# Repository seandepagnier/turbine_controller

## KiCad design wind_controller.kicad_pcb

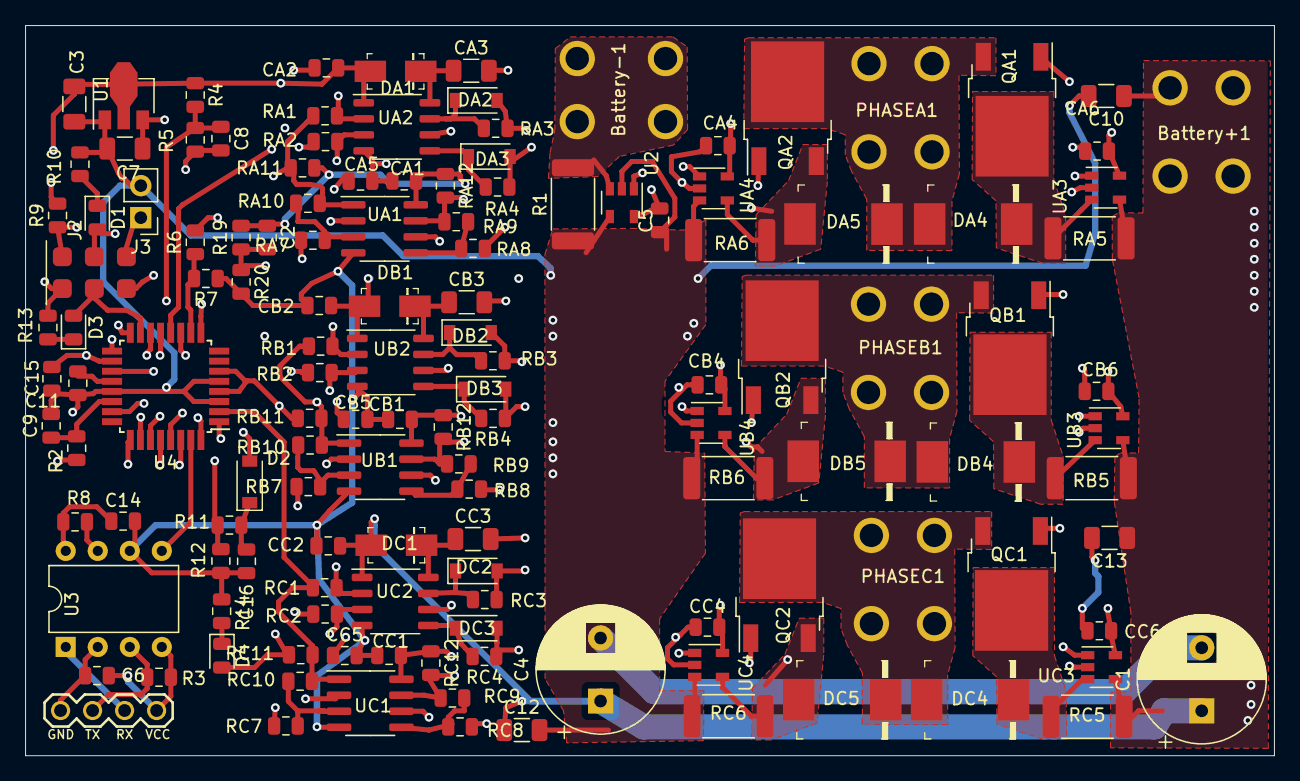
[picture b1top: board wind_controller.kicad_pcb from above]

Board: 4 copper layers, 99.1 x 57.9 mm, 135 parts (0 on the bottom side), 73 nets.

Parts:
Battery+1: Conn_01x01; screw_terminal
Battery-1: Conn_01x01; screw_terminal
C1, C4: 330uF; CP_Radial_D10.0mm_P5.00mm
C2, C9, C16: 1uF; C_0805_2012Metric
C3, C7, C10, C12, C13: 10uF; C_1206_3216Metric
C5, C6, C8, C11, C14, C15: .1uF; C_0805_2012Metric
CA1, CA4, CA5, CA6: .1uF; C_0805_2012Metric
CA2: 1uF; C_0805_2012Metric
CA3: 10uF; C_1206_3216Metric
CB1, CB4, CB5, CB6: .1uF; C_0805_2012Metric
CB2: 1uF; C_0805_2012Metric
CB3: 10uF; C_1206_3216Metric
CC1, CC4, CC5, CC6: .1uF; C_0805_2012Metric
CC2: 1uF; C_0805_2012Metric
CC3: 10uF; C_1206_3216Metric
D1: BLUE; LED_0805_2012Metric
D2: D; D_SOD-123
D3: GREEN; LED_0805_2012Metric
D4: RED; LED_0805_2012Metric
DA1: D; DO-214AC
DA2, DA3: D; D_SOD-123
DA4, DA5: D_Schottky; DO-214AB
DB1: D; DO-214AC
DB2, DB3: D; D_SOD-123
DB4, DB5: D_Schottky; DO-214AB
DC1: D; DO-214AC
DC2, DC3: D; D_SOD-123
DC4, DC5: D_Schottky; DO-214AB
J1: UART_Device; uart
J2: ISP
J3: start; PinHeader_1x02_P2.54mm_Vertical
PHASEA1: Conn_01x01; screw_terminal
PHASEB1: Conn_01x01; screw_terminal
PHASEC1: Conn_01x01; screw_terminal
QA1, QA2: nFET; TO-252-2
QB1, QB2: nFET; TO-252-2
QC1, QC2: nFET; TO-252-2
R1: .002; R_2512_6332Metric
R2, R5, R12: 100k; R_0805_2012Metric
R3, R8, R10, R13, R14: 2.4k; R_0805_2012Metric
R4, R11: 560k; R_0805_2012Metric
R6: 150k; R_0805_2012Metric
R7, R9, R20: 10k; R_0805_2012Metric
R19: 200k; R_0805_2012Metric
RA1, RA2: 100k; R_0805_2012Metric
RA3, RA4: 20; R_0805_2012Metric
RA5, RA6: .002; R_2512_6332Metric
RA7, RA8: 1k; R_0805_2012Metric
RA9, RA10: 200k; R_0805_2012Metric
RA11, RA12: 10k; R_0805_2012Metric
RB1, RB2: 100k; R_0805_2012Metric
RB3, RB4: 20; R_0805_2012Metric
RB5, RB6: .002; R_2512_6332Metric
RB7, RB8: 1k; R_0805_2012Metric
RB9, RB10: 200k; R_0805_2012Metric
RB11, RB12: 10k; R_0805_2012Metric
RC1, RC2: 100k; R_0805_2012Metric
RC3, RC4: 20; R_0805_2012Metric
RC5, RC6: .002; R_2512_6332Metric
RC7, RC8: 1k; R_0805_2012Metric
RC9, RC10: 200k; R_0805_2012Metric
RC11, RC12: 10k; R_0805_2012Metric
U1: HT75xx-1-SOT89; SOT-89-3
U2: INA180; SOT-23-5
U3: cpc5001; DIP-8_W7.62mm
U4: ATmega328-AU; TQFP-32_7x7mm_P0.8mm
UA1: LMV762; SOIC-8_3.9x4.9mm_P1.27mm
UA2: EG2132; SOP-8_3.9x4.9mm_P1.27mm
UA3, UA4: INA180; SOT-23-5
UB1: LMV762; SOIC-8_3.9x4.9mm_P1.27mm
UB2: EG2132; SOP-8_3.9x4.9mm_P1.27mm
UB3, UB4: INA180; SOT-23-5
UC1: LMV762; SOIC-8_3.9x4.9mm_P1.27mm
UC2: EG2132; SOP-8_3.9x4.9mm_P1.27mm
UC3, UC4: INA180; SOT-23-5

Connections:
+5V: C2.1, C5.1, C7.1, C14.1, C15.2, CA1.1, CA4.2, CA6.1, CB1.1, CB4.2, CB6.1, CC1.1, CC4.2, CC6.1, D4.2, J2.4, R8.2, R9.2, R19.2, RA11.1, RA12.1, RB11.1, RB12.1, RC11.1, RC12.1, U1.3, U2.5, U3.8, U4.4, U4.6, U4.18, UA1.8, UA3.5, UA4.5, UB1.8, UB3.5, UB4.5, UC1.8, UC3.5, UC4.5
/PhaseA/CURL: RA8.2, UA4.1
/PhaseB/CURL: RB8.2, UB4.1
/PhaseB/PHASE: CB3.2, DB4.2, DB5.1, PHASEB1.1, QB1.3, QB2.2, UB2.6
/PhaseC/CURL: RC8.2, UC4.1
/PhaseC/PHASE: CC3.2, DC4.2, DC5.1, PHASEC1.1, QC1.3, QC2.2, UC2.6
AH: RA1.1, U4.9, UA2.2
AHS: RA1.2, RA10.1, RA11.2, U4.32, UA1.1
AL: RA2.1, U4.26, UA2.3
ALS: RA2.2, RA9.1, RA12.2, U4.12, UA1.7
BH: RB1.1, U4.11, UB2.2
BHS: RB1.2, RB10.1, RB11.2, U4.1, UB1.1
BL: RB2.1, U4.27, UB2.3
BLS: RB2.2, RB9.1, RB12.2, U4.13, UB1.7
CH: RC1.1, U4.14, UC2.2
CHS: RC1.2, RC10.1, RC11.2, U4.2, UC1.1
CL: RC2.1, U4.28, UC2.3
CLS: RC2.2, RC9.1, RC12.2, U4.25, UC1.7
GND: C1.2, C3.2, C4.2, C5.2, C7.2, C8.2, C9.2, C10.2, C11.1, C12.2, C13.2, C14.2, C15.1, C16.2, CA1.2, CA2.2, CA5.2, CA6.2, CB1.2, CB2.2, CB5.2, CB6.2, CC1.2, CC2.2, CC5.2, CC6.2, J2.6, J3.2, R1.1, R5.2, R7.1, R10.2, R12.2, R13.2, R14.2, R20.2, RA6.1, RB6.1, RC6.1, U1.1, U2.2, U2.4, U3.6, U4.3, U4.5, U4.21, UA1.4, UA2.4, UA3.2, UA4.3, UB1.4, UB2.4, UB3.2, UB4.3, UC1.4, UC2.4, UC3.2, UC4.3
MISO: J2.1, J3.1, U4.16
MOSI: D3.2, J2.5, U4.15
unnamed: Battery-1.1, R1.2, U2.3
unnamed: C6.1, J1.1, R3.2, U3.4
unnamed: C6.2, J1.4, U3.2
unnamed: C8.1, R4.2, R5.1, U4.19
unnamed: C9.1, R2.2, U4.22
unnamed: C11.2, U4.20
unnamed: C16.1, D2.1, R11.1
unnamed: CA3.1, DA1.1, UA2.8
unnamed: CA4.1, DA5.2, QA2.3, RA6.2, UA4.2, UA4.4
unnamed: CB3.1, DB1.1, UB2.8
unnamed: CB4.1, DB5.2, QB2.3, RB6.2, UB4.2, UB4.4
unnamed: CC3.1, DC1.1, UC2.8
unnamed: CC4.1, DC5.2, QC2.3, RC6.2, UC4.2, UC4.4
unnamed: D1.1, R10.1
unnamed: D3.1, R13.1
unnamed: D4.1, R14.1
unnamed: DA2.1, RA3.2, UA2.7
unnamed: DA2.2, QA1.1, RA3.1
unnamed: DA3.1, RA4.2, UA2.5
unnamed: DA3.2, QA2.1, RA4.1
unnamed: DA4.1, QA1.2, RA5.1, UA3.3
unnamed: DB2.1, RB3.2, UB2.7
unnamed: DB2.2, QB1.1, RB3.1
unnamed: DB3.1, RB4.2, UB2.5
unnamed: DB3.2, QB2.1, RB4.1
unnamed: DB4.1, QB1.2, RB5.1, UB3.3
unnamed: DC2.1, RC3.2, UC2.7
unnamed: DC2.2, QC1.1, RC3.1
unnamed: DC3.1, RC4.2, UC2.5
unnamed: DC3.2, QC2.1, RC4.1
unnamed: DC4.1, QC1.2, RC5.1, UC3.3
unnamed: J1.2, U3.1
unnamed: J1.3, R3.1, U3.3
unnamed: R2.1, U2.1
unnamed: R6.1, R7.2, U4.10
unnamed: R11.2, R12.1, U4.23
unnamed: RA7.1, UA3.1
unnamed: RA8.1, RA9.2, UA1.5
unnamed: RA7.2, RA10.2, UA1.3
unnamed: RB7.1, UB3.1
unnamed: RB8.1, RB9.2, UB1.5
unnamed: RB7.2, RB10.2, UB1.3
unnamed: RC7.1, UC3.1
unnamed: RC8.1, RC9.2, UC1.5
unnamed: RC7.2, RC10.2, UC1.3
PHASEA: CA3.2, D2.2, DA4.2, DA5.1, PHASEA1.1, QA1.3, QA2.2, UA2.6
RESET: J2.3, R9.1, U4.29
RX: R8.1, U3.7, U4.30
SCK: D1.2, J2.2, U4.17
THRESH: C2.2, CA5.1, CB5.1, CC5.1, R19.1, R20.1, UA1.2, UA1.6, UB1.2, UB1.6, UC1.2, UC1.6
TX: U3.5, U4.31
VCC: Battery+1.1, C1.1, C3.1, C4.1, C10.1, C12.1, C13.1, CA2.1, CB2.1, CC2.1, DA1.2, DB1.2, DC1.2, R4.1, R6.2, RA5.2, RB5.2, RC5.2, U1.2, UA2.1, UA3.4, UB2.1, UB3.4, UC2.1, UC3.4

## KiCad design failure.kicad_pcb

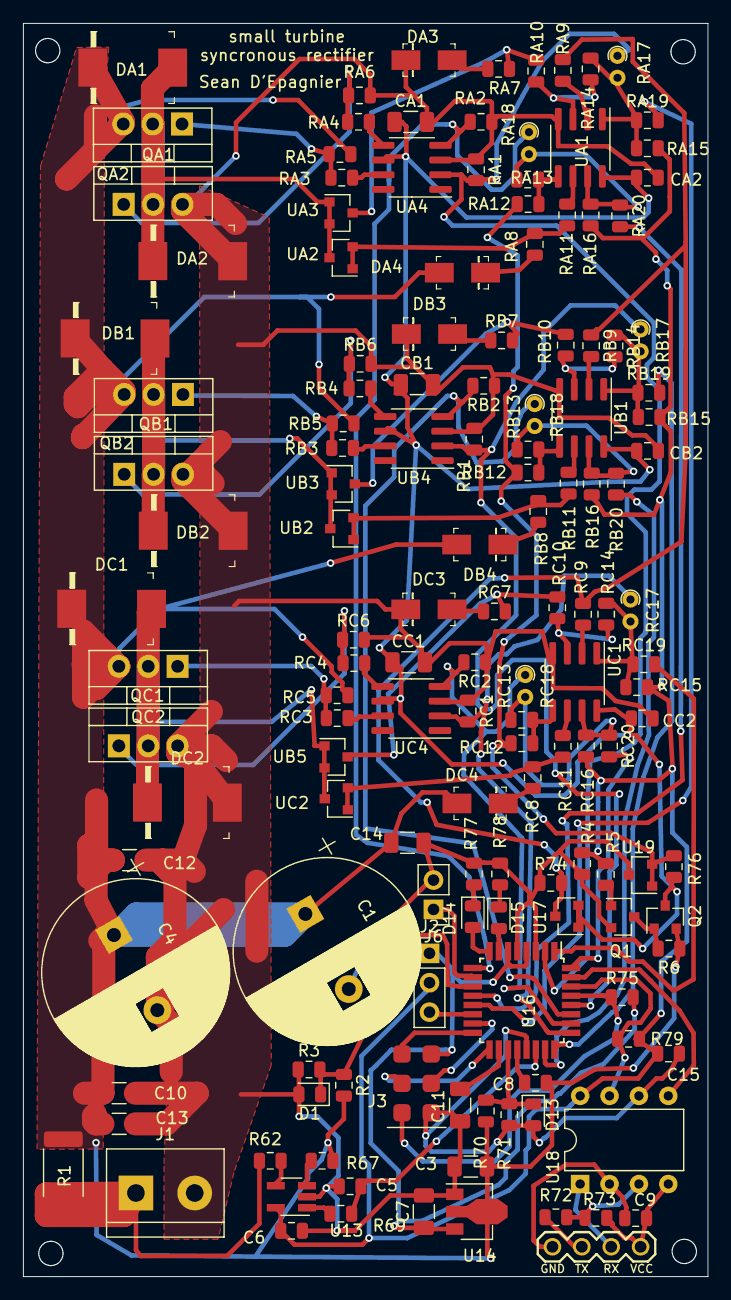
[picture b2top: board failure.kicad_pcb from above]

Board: 2 copper layers, 59.2 x 108.3 mm, 146 parts (0 on the bottom side), 92 nets.

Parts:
C1, C4: 680uF; CP_Radial_D16.0mm_P7.50mm
C3, C7, C10, C11, C12, C13, C14: 10uF; C_1206_3216Metric
C5: 1uF; C_0805_2012Metric
C6, C8, C9, C15: .1uF; C_0805_2012Metric
CA1: 10uF; C_1206_3216Metric
CA2: .1uF; C_0805_2012Metric
CB1: 10uF; C_1206_3216Metric
CB2: .1uF; C_0805_2012Metric
CC1: 10uF; C_1206_3216Metric
CC2: .1uF; C_0805_2012Metric
D1, D13: 3v3; D_0805_2012Metric
D14: RED; LED_0805_2012Metric
D15: BLUE; LED_0805_2012Metric
DA1, DA2: D_Schottky; DO-214AB
DA3, DA4: D; DO-214AC
DB1, DB2: D_Schottky; DO-214AB
DB3, DB4: D; DO-214AC
DC1, DC2: D_Schottky; DO-214AB
DC3, DC4: D; DO-214AC
J1: Conn_01x02; TerminalBlock_bornier-2_P5.08mm
J2: Conn_01x03; PinHeader_1x03_P2.54mm_Vertical
J3: ISP
J5: UART_Device; uart
J6: Stop; PinHeader_1x02_P2.54mm_Vertical
Q1: npn; SOT-23
Q2: pFET; SOT-23
QA1: pFET; TO-220-3_Vertical
QA2: nFET; TO-220-3_Vertical
QB1: pFET; TO-220-3_Vertical
QB2: nFET; TO-220-3_Vertical
QC1: pFET; TO-220-3_Vertical
QC2: nFET; TO-220-3_Vertical
R1: .002; R_2512_6332Metric
R2: 150k; R_0805_2012Metric
R3, R6, R71, R75: 10k; R_0805_2012Metric
R4, R5, R69, R74, R76: 100k; R_0805_2012Metric
R62, R67: 20; R_0805_2012Metric
R70: 56k; R_0805_2012Metric
R72: 560; R_0805_2012Metric
R73: 2k; R_0805_2012Metric
R77, R78, R79: 2.4k; R_0805_2012Metric
RA1, RA2: 1M; R_0805_2012Metric
RA3, RA4: 20; R_0805_2012Metric
RA5, RA6, RA7, RA8, RA19, RA20: 100k; R_0805_2012Metric
RA9, RA10, RA11, RA12, RA15, RA16: 10k; R_0805_2012Metric
RA13, RA14: 10M; R_0805_2012Metric
RA17, RA18: 0; R_Axial_DIN0204_L3.6mm_D1.6mm_P1.90mm_Vertical
RB1, RB2: 1M; R_0805_2012Metric
RB3, RB4: 20; R_0805_2012Metric
RB5, RB6, RB7, RB8, RB19, RB20: 100k; R_0805_2012Metric
RB9, RB10, RB11, RB12, RB15, RB16: 10k; R_0805_2012Metric
RB13, RB14: 10M; R_0805_2012Metric
RB17, RB18: 0; R_Axial_DIN0204_L3.6mm_D1.6mm_P1.90mm_Vertical
RC1, RC2: 1M; R_0805_2012Metric
RC3, RC4: 20; R_0805_2012Metric
RC5, RC6, RC7, RC8, RC19, RC20: 100k; R_0805_2012Metric
RC9, RC10, RC11, RC12, RC15, RC16: 10k; R_0805_2012Metric
RC13, RC14: 10M; R_0805_2012Metric
RC17, RC18: 0; R_Axial_DIN0204_L3.6mm_D1.6mm_P1.90mm_Vertical
U13: INA180; SOT-23-5_HandSoldering
U14: HT75xx-1-SOT89; SOT-89-3
U16: ATmega328-AU; TQFP-32_7x7mm_P0.8mm
U17, U19: CJ431; SOT-23
U18: cpc5001; DIP-8_W7.62mm
UA1: LM393; SOIC-8_3.9x4.9mm_P1.27mm
UA2, UA3: CJ431; SOT-23
UA4: MIC4428; SOIC-8_3.9x4.9mm_P1.27mm
UB1: LM393; SOIC-8_3.9x4.9mm_P1.27mm
UB2, UB3, UB5: CJ431; SOT-23
UB4: MIC4428; SOIC-8_3.9x4.9mm_P1.27mm
UC1: LM393; SOIC-8_3.9x4.9mm_P1.27mm
UC2: CJ431; SOT-23
UC4: MIC4428; SOIC-8_3.9x4.9mm_P1.27mm

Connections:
+2V5: R76.1, RA12.1, RB12.1, RC12.1, U19.1, U19.2
+5V: C7.1, J2.1, J3.4, R75.2, U14.3, U16.4, U16.6
+5VD: C6.1, C15.1, J2.2, R4.1, R5.1, R79.2, RA15.1, RA16.1, RB15.1, RB16.1, RC15.1, RC16.1, U13.5, U18.8
-2V5: R74.2, RA9.1, RB9.1, RC9.1, U17.3
AH: RA1.2, RA17.1, U16.2, UA4.2
AHS: RA19.2, U16.13
AL: RA2.2, RA18.1, U16.9, UA4.4
ALS: RA20.2, U16.12
BH: RB1.2, RB17.1, U16.28, UB4.2
BHS: RB19.2, U16.24
BL: RB2.2, RB18.1, U16.27, UB4.4
BLS: RB20.2, U16.23
CH: RC1.2, RC17.1, U16.25, UC4.2
CHS: RC19.2, U16.1
CL: RC2.2, RC18.1, U16.26, UC4.4
CLS: RC20.2, U16.32
GND: C1.2, C3.2, C4.2, C5.2, C6.2, C7.2, C10.2, C11.2, C12.2, C13.2, C14.2, C15.2, CA1.2, CA2.2, CB1.2, CB2.2, CC1.2, CC2.2, D1.2, D13.2, DA2.2, DA3.1, DB2.2, DB3.1, DC2.2, DC3.1, J1.2, J3.6, J6.2, Q1.2, QA2.3, QB2.3, QC2.3, R3.1, R4.2, R71.1, R74.1, R77.1, R78.1, RA1.1, RA2.1, RA6.2, RB1.1, RB2.1, RB6.2, RC1.1, RC2.1, RC6.2, U13.2, U14.1, U16.3, U16.5, U16.21, U18.6, U19.3, UA1.4, UA4.3, UB1.4, UB4.3, UC1.4, UC4.3
MISO: J3.1, U16.16
MOSI: J3.5, U16.15
unnamed: C5.1, R69.2, U16.22
unnamed: C8.2, U16.20
unnamed: C9.1, J5.1, R73.1, U18.4
unnamed: C9.2, J5.4, U18.2
unnamed: C11.1, U16.18
unnamed: D1.1, R2.1, R3.2, U16.11
unnamed: D13.1, R70.2, R71.2, U16.19
unnamed: D14.1, R77.2
unnamed: D14.2, U16.8
unnamed: D15.1, R78.2
unnamed: D15.2, U16.7
unnamed: DA3.2, RA7.1
unnamed: DA4.1, RA8.2
unnamed: DB3.2, RB7.1
unnamed: DB4.1, RB8.2
unnamed: DC3.2, RC7.1
unnamed: DC4.1, RC8.2
unnamed: J1.1, R1.2, R62.2
unnamed: J2.3, U16.14
unnamed: J5.2, U18.1
unnamed: J5.3, R72.2
unnamed: J6.1, U16.10
unnamed: Q1.1, R5.2
unnamed: Q1.3, Q2.1, R6.2
unnamed: QA1.1, RA3.1, RA5.2
unnamed: QA2.1, RA4.1, RA6.1
unnamed: QB1.1, RB3.1, RB5.2
unnamed: QB2.1, RB4.1, RB6.1
unnamed: QC1.1, RC3.1, RC5.2
unnamed: QC2.1, RC4.1, RC6.1
unnamed: R62.1, U13.4
unnamed: R67.1, U13.3
unnamed: R69.1, U13.1
unnamed: R72.1, R73.2, U18.3
unnamed: RA3.2, UA4.7
unnamed: RA4.2, UA4.5
unnamed: RA9.2, UA1.2
unnamed: RA7.2, RA10.1, UA3.3
unnamed: RA10.2, RA14.2, UA1.3
unnamed: RA8.1, RA11.1, UA2.1, UA2.2
unnamed: RA11.2, UA1.6
unnamed: RA12.2, RA13.2, UA1.5
unnamed: RA13.1, RA16.2, RA18.2, RA20.1, UA1.7
unnamed: RA14.1, RA15.2, RA17.2, RA19.1, UA1.1
unnamed: RB3.2, UB4.7
unnamed: RB4.2, UB4.5
unnamed: RB9.2, UB1.2
unnamed: RB7.2, RB10.1, UB3.3
unnamed: RB10.2, RB14.2, UB1.3
unnamed: RB8.1, RB11.1, UB2.1, UB2.2
unnamed: RB11.2, UB1.6
unnamed: RB12.2, RB13.2, UB1.5
unnamed: RB13.1, RB16.2, RB18.2, RB20.1, UB1.7
unnamed: RB14.1, RB15.2, RB17.2, RB19.1, UB1.1
unnamed: RC3.2, UC4.7
unnamed: RC4.2, UC4.5
unnamed: RC9.2, UC1.2
unnamed: RC7.2, RC10.1, UB5.3
unnamed: RC10.2, RC14.2, UC1.3
unnamed: RC8.1, RC11.1, UC2.1, UC2.2
unnamed: RC11.2, UC1.6
unnamed: RC12.2, RC13.2, UC1.5
unnamed: RC13.1, RC16.2, RC18.2, RC20.1, UC1.7
unnamed: RC14.1, RC15.2, RC17.2, RC19.1, UC1.1
PHASEA: DA1.2, DA2.1, QA1.2, QA2.2, UA2.3, UA3.1, UA3.2
PHASEB: DB1.2, DB2.1, QB1.2, QB2.2, UB2.3, UB3.1, UB3.2
PHASEC: DC1.2, DC2.1, QC1.2, QC2.2, UB5.1, UB5.2, UC2.3
RESET: J3.3, R75.1, U16.29
RX: R79.1, U16.30, U18.7
SCK: J3.2, U16.17
TX: U16.31, U18.5
VCC: C1.1, C3.1, C4.1, C8.1, C10.1, C12.1, C13.1, C14.1, DA1.1, DA4.2, DB1.1, DB4.2, DC1.1, DC4.2, Q2.2, QA1.3, QB1.3, QC1.3, R1.1, R2.2, R6.1, R67.2, R70.1, RA5.1, RB5.1, RC5.1, U14.2
VDD: CA1.1, CA2.1, CB1.1, CB2.1, CC1.1, CC2.1, Q2.3, R76.2, U17.1, U17.2, UA1.8, UA4.6, UB1.8, UB4.6, UC1.8, UC4.6

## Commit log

2023-02-12 add iles
2023-02-12 add library
2023-02-12 rename stuff
